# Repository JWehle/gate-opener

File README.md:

# gate-opener
Control electronics for opening a wooden gate with a linear actuator.

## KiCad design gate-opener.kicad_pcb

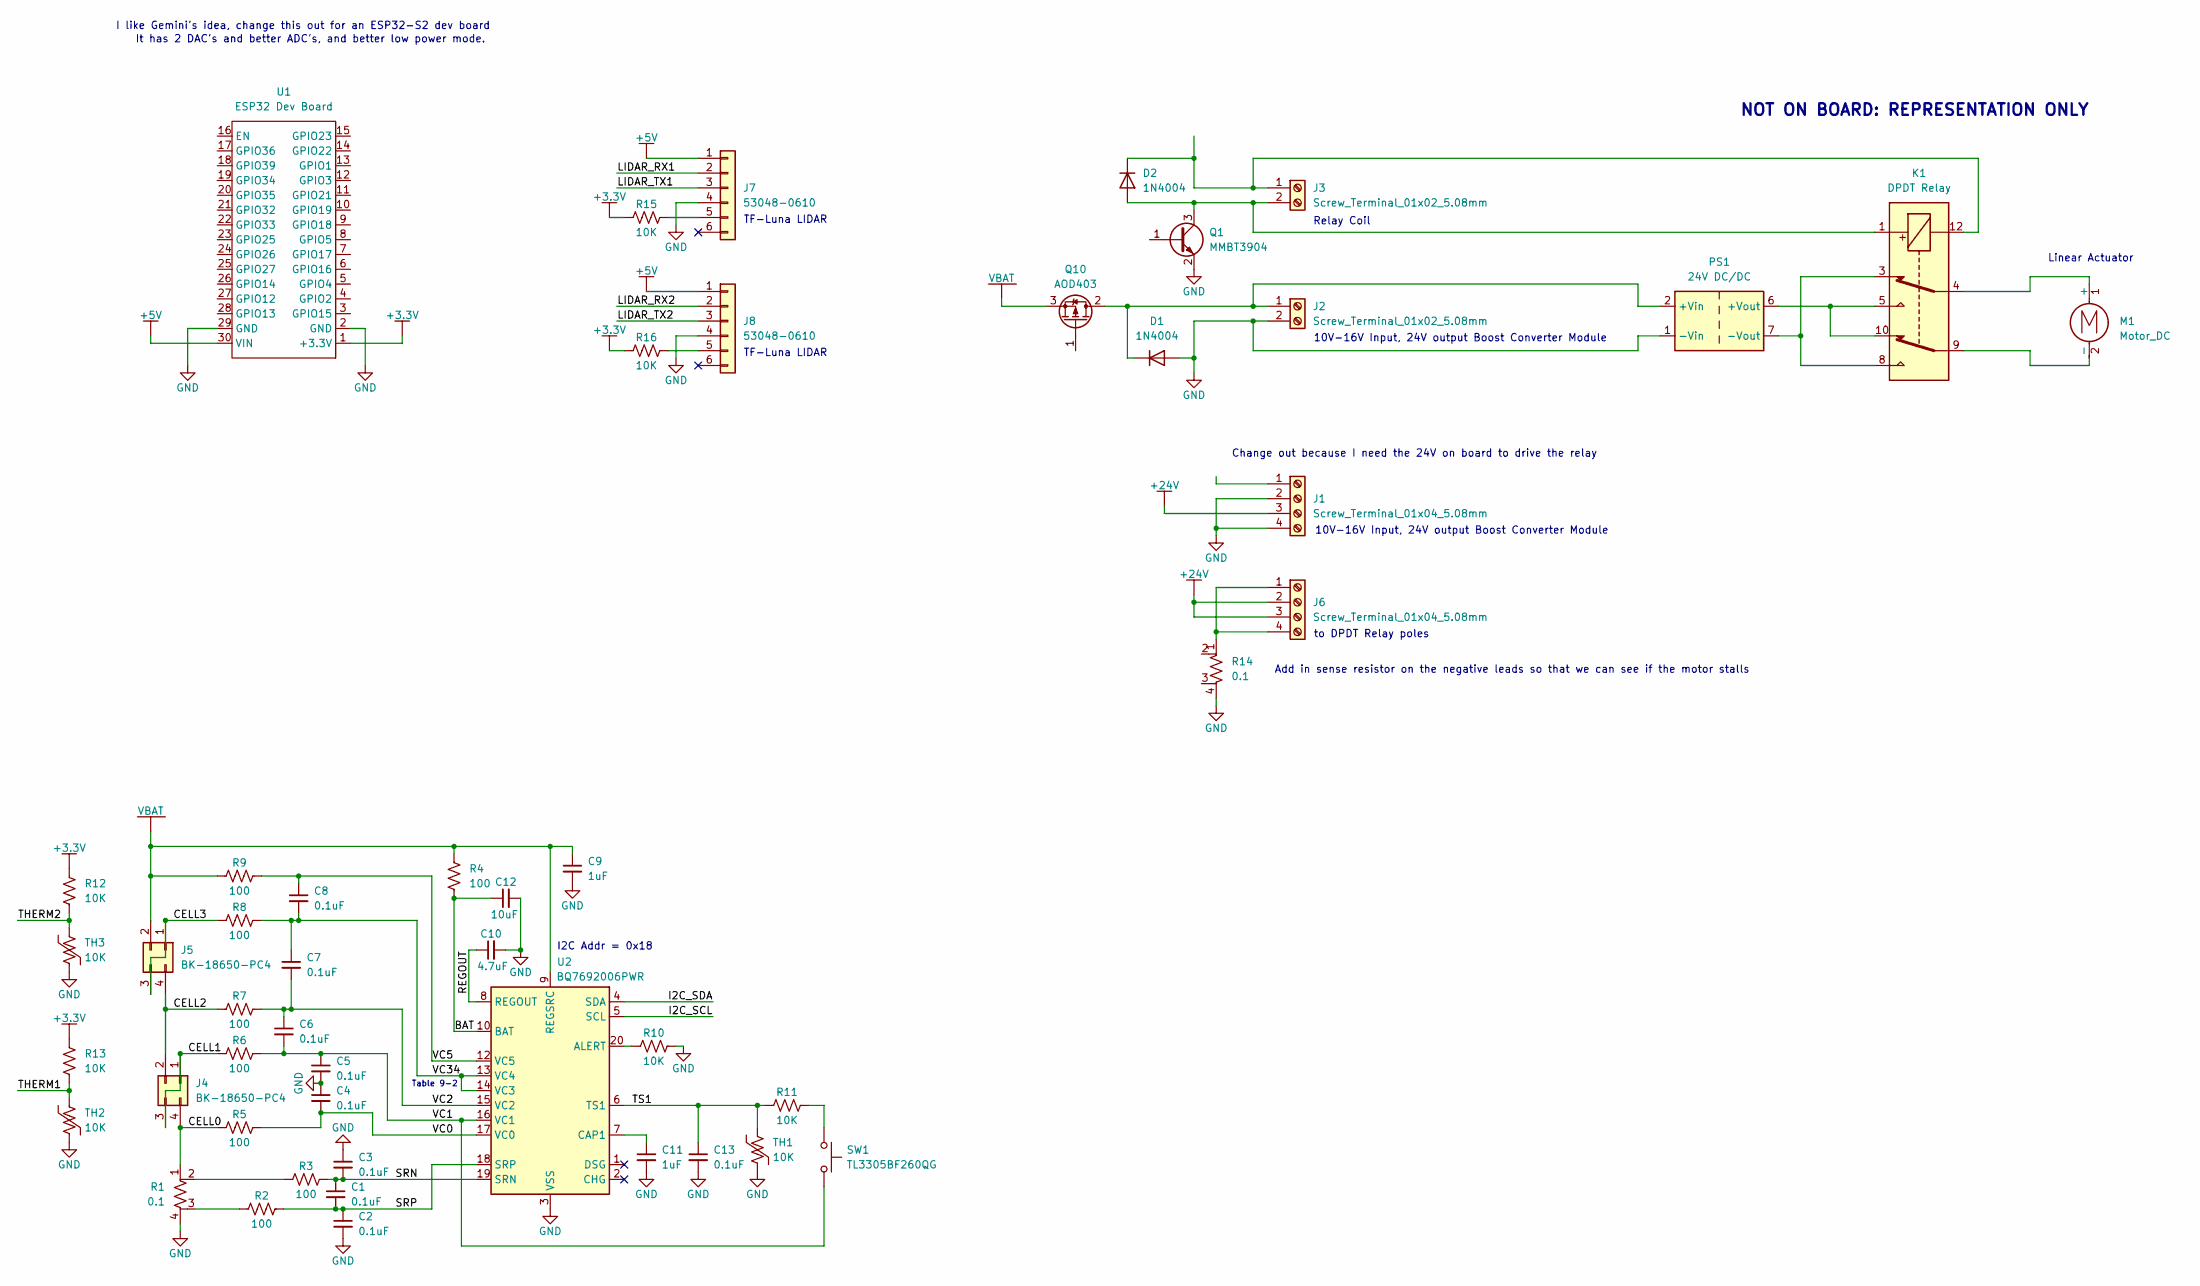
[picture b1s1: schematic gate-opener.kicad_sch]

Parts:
C1, C2, C3, C4, C5, C6, C7, C8, C13: 0.1uF; C_0603_1608Metric_Pad1.08x0.95mm_HandSolder
C9, C11: 1uF; C_0603_1608Metric_Pad1.08x0.95mm_HandSolder
C10: 4.7uF; C_0603_1608Metric_Pad1.08x0.95mm_HandSolder
C12: 10uF; C_0603_1608Metric_Pad1.08x0.95mm_HandSolder
D1, D2: 1N4004; D_DO-41_SOD81_P10.16mm_Horizontal
J1, J6: Screw_Terminal_01x04_5.08mm; TerminalBlock_bornier-4_P5.08mm
J2, J3: Screw_Terminal_01x02_5.08mm; TerminalBlock_bornier-2_P5.08mm
J4, J5: BK-18650-PC4; BK-18650-PC4_MPD
J7, J8: 53048-0610; Molex_PicoBlade_53048-0610_1x06_P1.25mm_Horizontal
K1: DPDT Relay; Relay_DPDT_Kemet_EC2_NU
M1: Motor_DC
PS1: 24V DC/DC; Converter_DCDC_XP_POWER-ITXxxxxSA_THT
Q1: MMBT3904; SOT-23
Q10: AOD403; TO-252-2
R1, R14: 0.1; R_Shunt_Vishay_WSK2512_6332Metric_T2.21mm
R2, R3, R4, R5, R6, R7, R8, R9: 100; R_0603_1608Metric_Pad0.98x0.95mm_HandSolder
R10, R11, R12, R13, R15, R16: 10K; R_0603_1608Metric_Pad0.98x0.95mm_HandSolder
SW1: TL3305BF260QG; SW_SPST_TL3305B
TH1, TH2, TH3: 10K; R_Axial_DIN0204_L3.6mm_D1.6mm_P2.54mm_Vertical
U1: ESP32 Dev Board; ESP32_MODULE
U2: BQ7692006PWR; TSSOP-20_4.4x6.5mm_P0.65mm

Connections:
+3.3V: R12.2, R13.2, R15.1, R16.1, U1.1 (+3.3V)
+5V: J7.1, J8.1, U1.30 (VIN)
+24V: J1.3, J6.2, J6.3
/BAT: C12.1, R4.1, U2.10 (BAT)
/CELL0: J4.4, R1.1, R5.1
/CELL1: J4.1, J4.3, R6.1
/CELL2: J4.2, J5.4, R7.1
/CELL3: J5.1, J5.3, R8.1
/I2C_SCL: U2.5 (SCL)
/I2C_SDA: U2.4 (SDA)
/LIDAR_RX1: J7.2
/LIDAR_RX2: J8.2
/LIDAR_TX1: J7.3
/LIDAR_TX2: J8.3
/REGOUT: C10.1, U2.8 (REGOUT)
/SRN: C1.1, C3.2, R3.2, U2.19 (SRN)
/SRP: C1.2, C2.1, R2.2, U2.18 (SRP)
/THERM1: R13.1, TH2.1
/THERM2: R12.1, TH3.1
/TS1: C13.1, R11.1, TH1.1, U2.6 (TS1)
/VC0: C4.2, R5.2, U2.17 (VC0)
/VC1: C5.1, C6.2, R6.2, SW1.2, U2.16 (VC1)
/VC2: C6.1, C7.2, R7.2, U2.15 (VC2)
/VC5: C8.1, R9.2, U2.12 (VC5)
/VC34: C7.1, C8.2, R8.2, U2.13 (VC4), U2.14 (VC3)
GND: C2.2, C3.1, C4.1, C5.2, C9.2, C10.2, C11.2, C12.2, C13.2, D1.2 (A), J1.2, J1.4, J2.2, J7.4, J8.4, PS1.1 (-Vin), Q1.2 (E), R1.4, R10.2, R14.4, TH1.2, TH2.2, TH3.2, U1.2 (GND), U1.29 (GND), U2.3 (VSS)
unnamed: D1.1 (K), J2.1, PS1.2 (+Vin), Q10.2 (D)
unnamed: D2.2 (A), J3.2, K1.1, Q1.3 (C)
unnamed: D2.1 (K), J3.1, K1.12
unnamed: J6.1, J6.4, R14.1
unnamed: J7.5, R15.2
unnamed: J8.5, R16.2
unnamed: K1.3, K1.8, PS1.7 (-Vout)
unnamed: K1.4, M1.1 (+)
unnamed: K1.9, M1.2 (-)
unnamed: K1.5, K1.10, PS1.6 (+Vout)
unnamed: R1.2, R3.1
unnamed: R1.3, R2.1
unnamed: R11.2, SW1.1
unnamed: R10.1, U2.20 (ALERT)
unnamed: C11.1, U2.7 (CAP1)
VBAT: C9.1, J5.2, Q10.3 (S), R4.2, R9.1, U2.9 (REGSRC)

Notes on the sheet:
Add in sense resistor on the negative leads so that we can see if the motor stalls
NOT ON BOARD: REPRESENTATION ONLY
Relay Coil
I like Gemini's idea, change this out for an ESP32-S2 dev board
It has 2 DAC's and better ADC's, and better low power mode.
TF-Luna LIDAR
Linear Actuator
10V-16V Input, 24V output Boost Converter Module
to DPDT Relay poles
I2C Addr = 0x18
Change out because I need the 24V on board to drive the relay
Table 9-2

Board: 2 copper layers, 47 parts (0 on the bottom side), 32 nets, no tracks yet.

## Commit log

2026-03-03 schematic init
2026-03-03 schematic
